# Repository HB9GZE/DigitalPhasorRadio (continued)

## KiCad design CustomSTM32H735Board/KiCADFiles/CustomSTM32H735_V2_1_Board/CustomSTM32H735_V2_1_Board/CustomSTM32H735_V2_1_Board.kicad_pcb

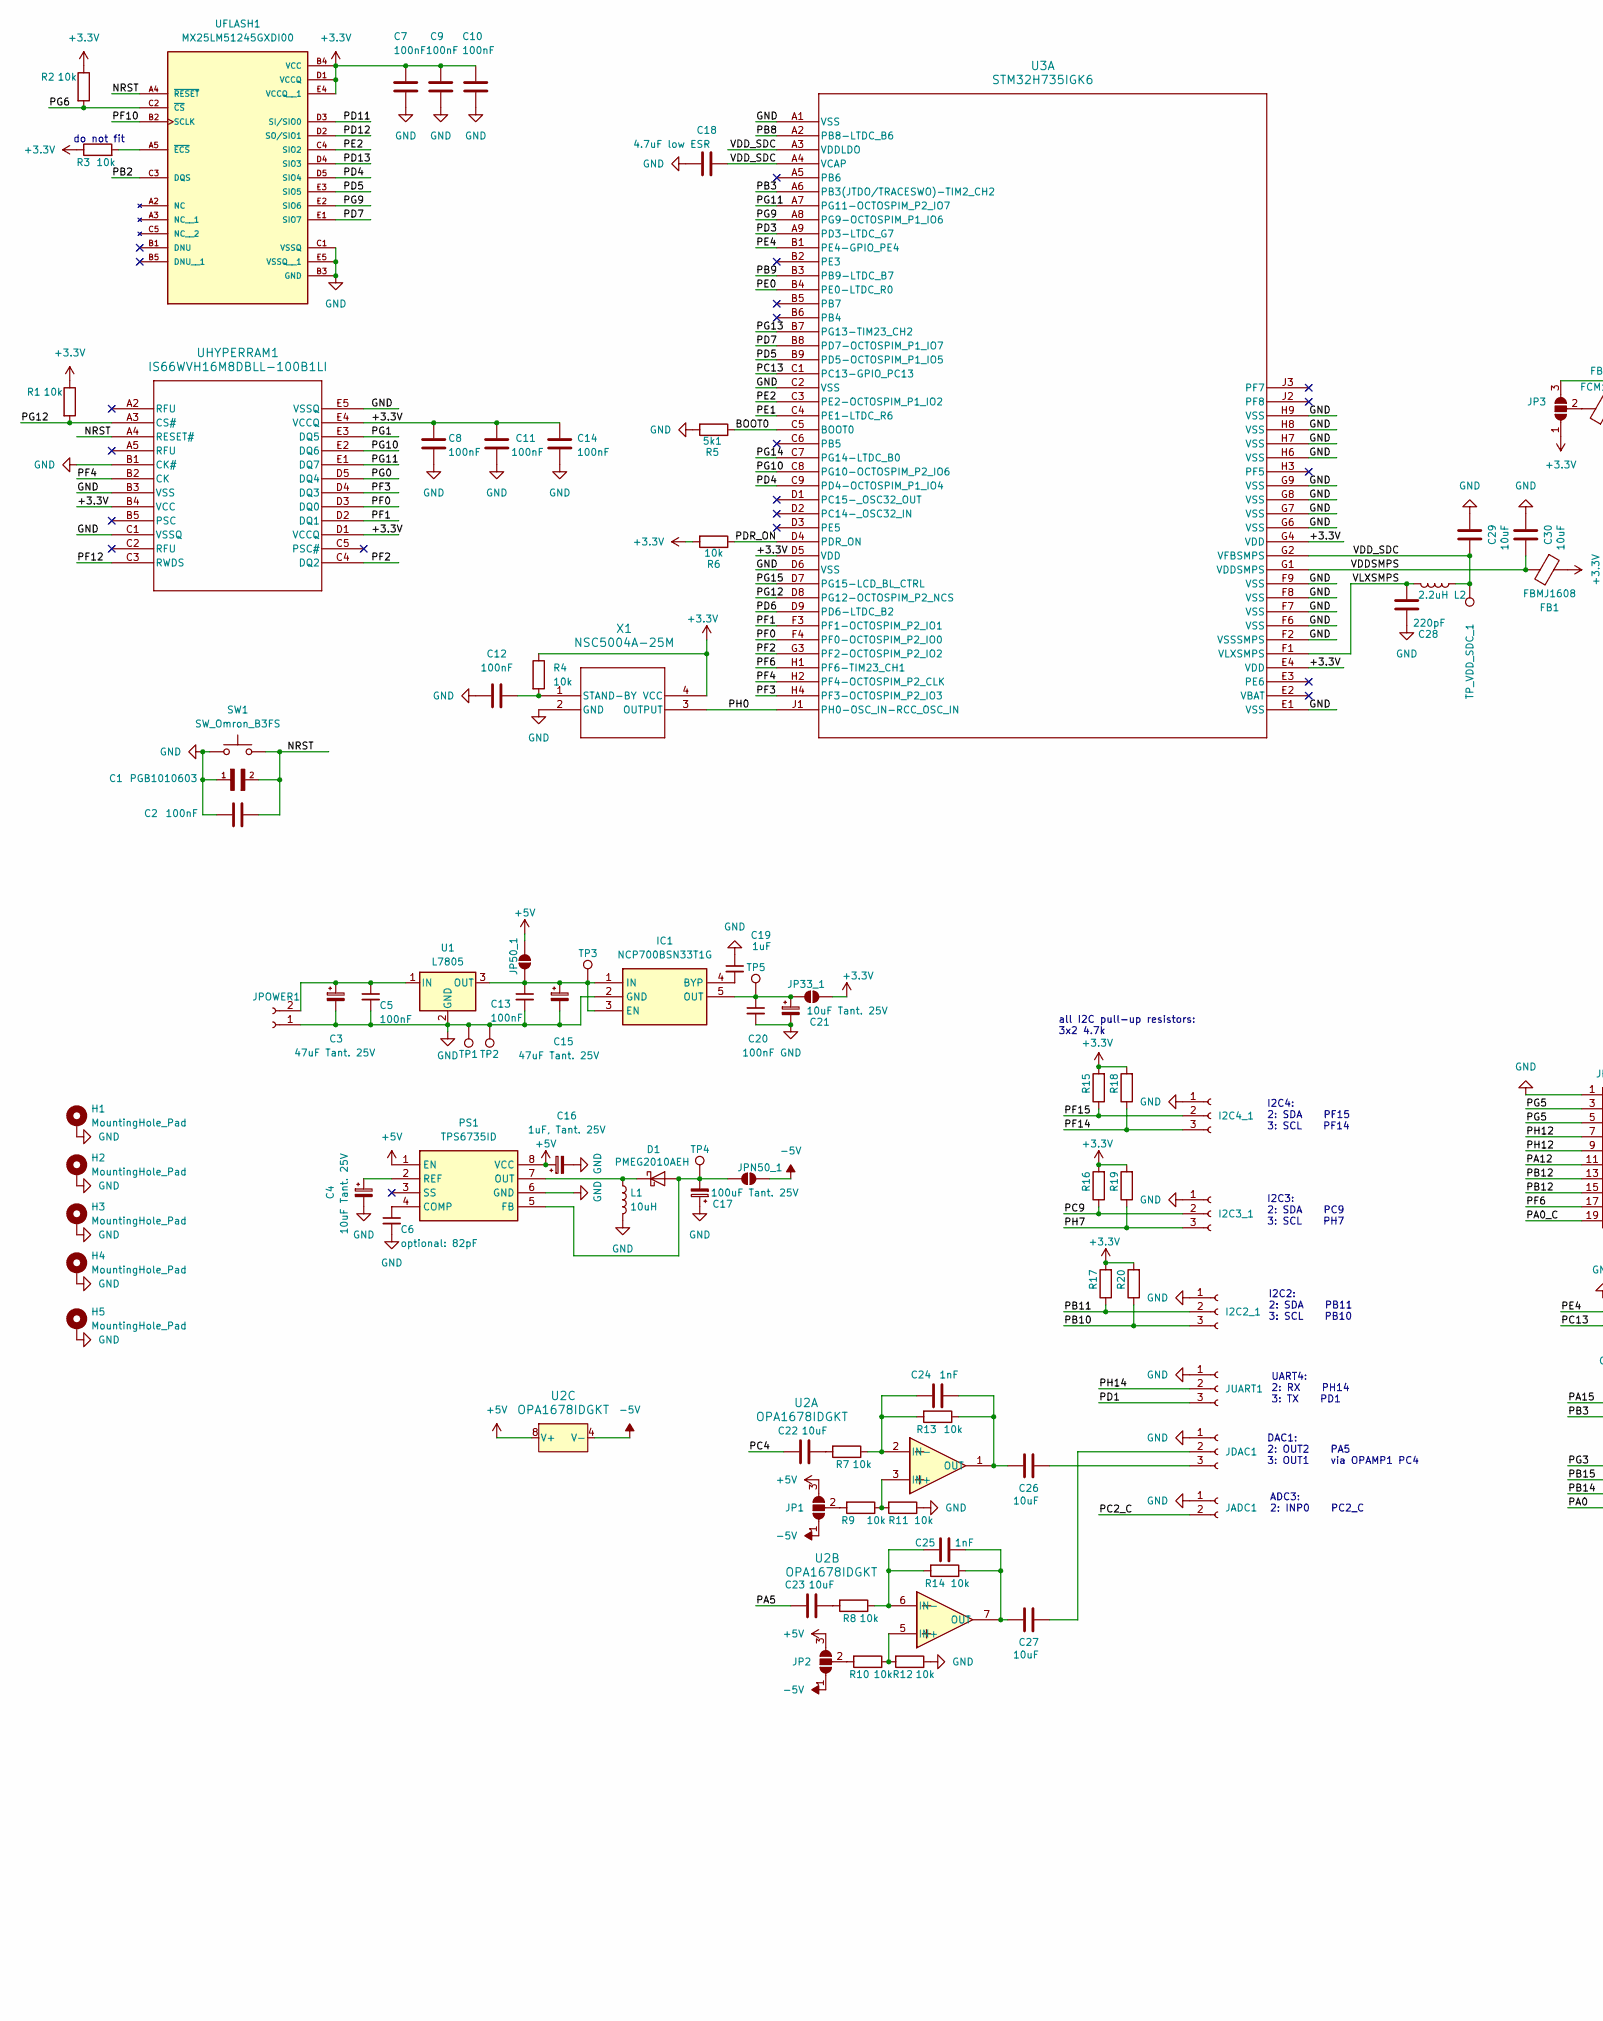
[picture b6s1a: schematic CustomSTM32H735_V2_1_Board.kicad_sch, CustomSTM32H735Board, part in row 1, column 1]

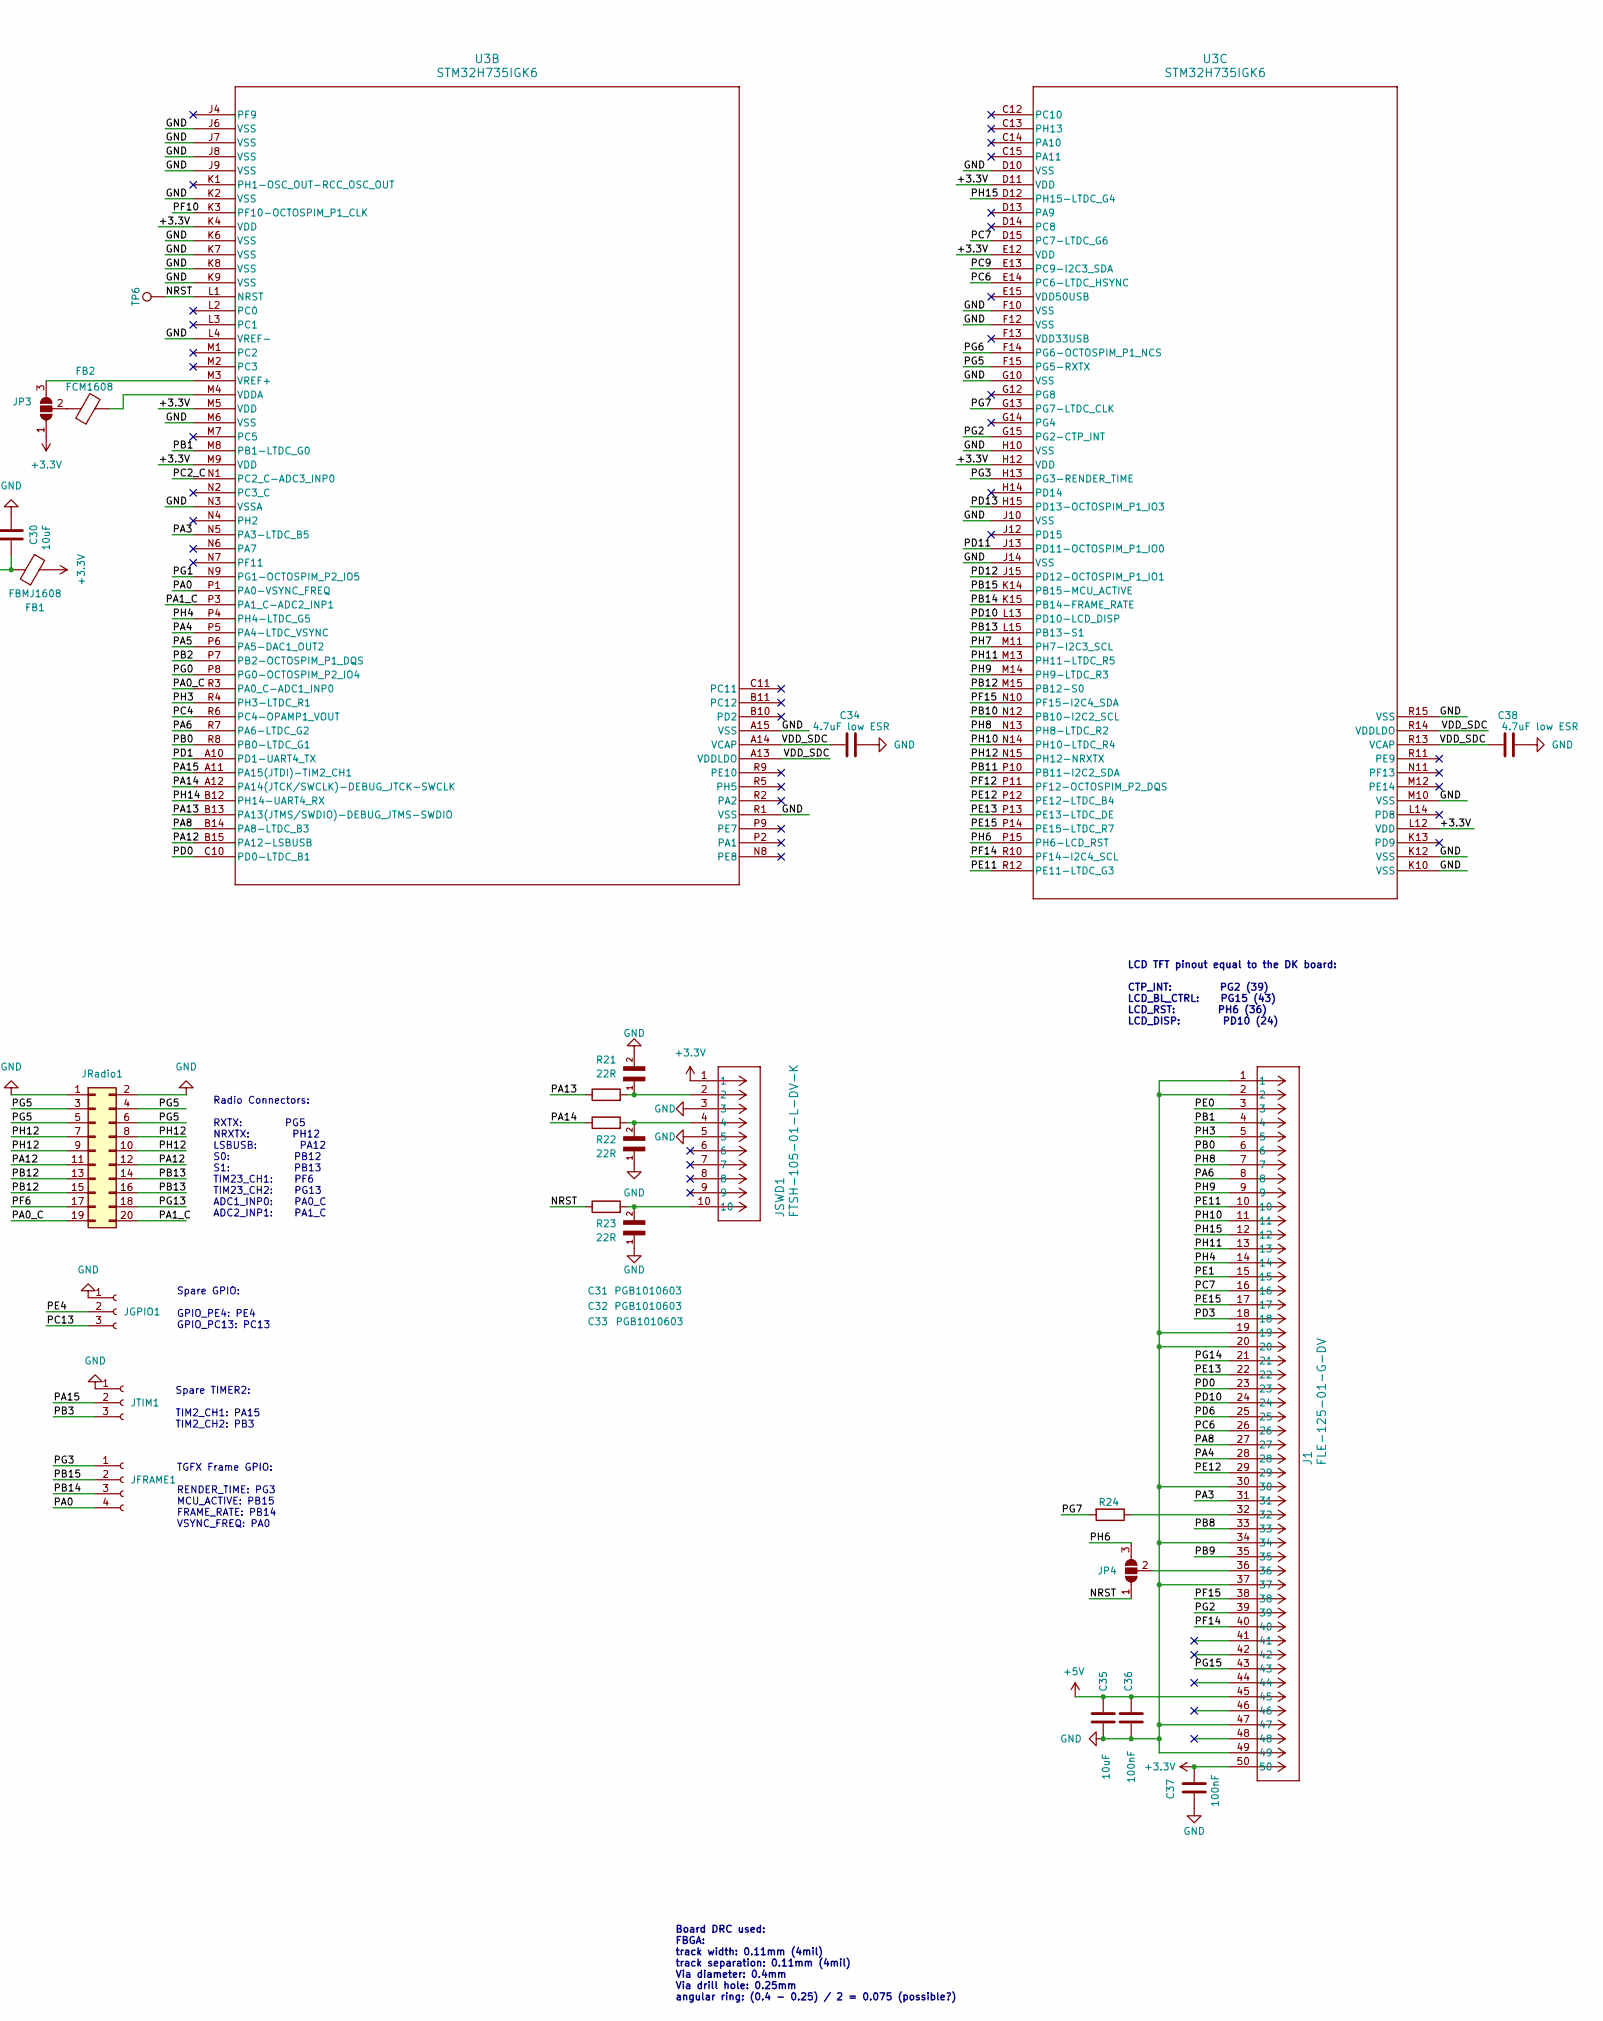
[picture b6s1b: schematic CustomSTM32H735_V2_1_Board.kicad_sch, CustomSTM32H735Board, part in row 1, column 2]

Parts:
C1, C31, C32, C33: PGB1010603; C_0603_1608Metric
C2, C5, C7, C8, C9, C10, C11, C12, C13, C14, C20, C36, C37: 100nF; C_0805_2012Metric_Pad1.18x1.45mm_HandSolder
C3, C15: 47uF Tant. 25V; CP_EIA-6032-20_AVX-F_Pad2.25x2.35mm_HandSolder
C4, C21: 10uF Tant. 25V; CP_EIA-6032-20_AVX-F_Pad2.25x2.35mm_HandSolder
C6: optional: 82pF; C_0805_2012Metric_Pad1.18x1.45mm_HandSolder
C16: 1uF, Tant. 25V; CP_EIA-6032-20_AVX-F_Pad2.25x2.35mm_HandSolder
C17: 100uF Tant. 25V; CP_EIA-6032-20_AVX-F_Pad2.25x2.35mm_HandSolder
C18, C34, C38: 4.7uF low ESR; C_0805_2012Metric_Pad1.18x1.45mm_HandSolder
C19: 1uF; C_0805_2012Metric_Pad1.18x1.45mm_HandSolder
C22, C23, C26, C27, C29, C30, C35: 10uF; C_0805_2012Metric_Pad1.18x1.45mm_HandSolder
C24, C25: 1nF; C_0805_2012Metric_Pad1.18x1.45mm_HandSolder
C28: 220pF; C_0805_2012Metric_Pad1.18x1.45mm_HandSolder
D1: PMEG2010AEH; D_SOD-123F
FB1: FBMJ1608; L_0603_1608Metric_Pad1.05x0.95mm_HandSolder
FB2: FCM1608; L_0603_1608Metric_Pad1.05x0.95mm_HandSolder
H1, H2, H3, H4, H5: MountingHole_Pad; MountingHole_3.2mm_M3_Pad_TopBottom
I2C2_1, I2C3_1, I2C4_1: Conn_01x03_Socket; JST_XH_B3B-XH-A_1x03_P2.50mm_Vertical
IC1: NCP700BSN33T1G; SOT95P275X120-5N; Manufacturer_Part_Number NCP700BSN33T1G; Mouser Part Number 863-NCP700BSN33T1G
J1: FLE-125-01-G-DV; CON50_2X25_UF_FLE_SAI
JADC1: Conn_01x02_Socket; JST_XH_B2B-XH-A_1x02_P2.50mm_Vertical
JDAC1: Conn_01x03_Socket; JST_XH_B3B-XH-A_1x03_P2.50mm_Vertical
JFRAME1: Conn_01x04_Socket; JST_XH_B4B-XH-A_1x04_P2.50mm_Vertical
JGPIO1: Conn_01x03_Socket; JST_XH_B3B-XH-A_1x03_P2.50mm_Vertical
JP1, JP2, JP3, JP4: SolderJumper_3_Open; SolderJumper-3_P1.3mm_Open_Pad1.0x1.5mm_NumberLabels
JP33_1, JP50_1: SolderJumper_2_Open; SolderJumper-2_P1.3mm_Open_Pad1.0x1.5mm
JPN50_1: SolderJumper_2_Open; SolderJumper-2_P1.3mm_Open_Pad1.0x1.5mm
JPOWER1: Conn_01x02_Socket; JST_XH_B2B-XH-A_1x02_P2.50mm_Vertical
JRadio1: Conn_02x10_Odd_Even; IDC-Header_2x10_P2.54mm_Vertical
JSWD1: FTSH-105-01-L-DV-K; CON10_2X5_DUK_FTSH_SAI-M
JTIM1: Conn_01x03_Socket; JST_XH_B3B-XH-A_1x03_P2.50mm_Vertical
JUART1: Conn_01x03_Socket; JST_XH_B3B-XH-A_1x03_P2.50mm_Vertical
L1: 10uH; L_1812_4532Metric_Pad1.30x3.40mm_HandSolder
L2: 2.2uH; L_Murata_DFE201610P
PS1: TPS6735ID; SOIC127P600X175-8N; Manufacturer_Part_Number TPS6735ID; Mouser Part Number 595-TPS6735ID
R1, R2, R3, R4, R6, R7, R8, R9, R10, R11, R12, R13, R14: 10k; R_0805_2012Metric_Pad1.20x1.40mm_HandSolder
R5: 5k1; R_0805_2012Metric_Pad1.20x1.40mm_HandSolder
R15, R16, R17, R18, R19, R20: 4.7k; R_0805_2012Metric_Pad1.20x1.40mm_HandSolder
R21, R22, R23: 22R; R_0805_2012Metric_Pad1.20x1.40mm_HandSolder
R24: 0R; R_0805_2012Metric_Pad1.20x1.40mm_HandSolder
SW1: SW_Omron_B3FS; SW_SPST_Omron_B3FS-100xP
TP1, TP2, TP3, TP4, TP5, TP6: TestPoint; Pin_D0.7mm_L6.5mm_W1.8mm_FlatFork
TP_VDD_SDC_1: TestPoint; Pin_D0.7mm_L6.5mm_W1.8mm_FlatFork
U1: L7805; TO-220-3_Horizontal_TabDown_GND_Pad
U2: OPA1678IDGKT; OPA1678_L
U3: STM32H735IGK6; BGA_735IGK6_STM
UFLASH1: MX25LM51245GXDI00; BGA24C100P5X5_600X800X120; PARTREV 1.1
UHYPERRAM1: IS66WVH16M8DBLL-100B1LI; TFBGA24_6X8_ISI
X1: NSC5004A-25M; NSC5004_NDK

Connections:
+3.3V: C7.1, C8.1, C9.1, C10.1, C11.1, C14.1, C37.1, FB1.1, J1.50, JP3.1 (A), JP33_1.2 (B), JSWD1.1, R1.1, R2.1, R3.1, R4.1, R6.2, R15.2, R16.2, R17.2, R18.2, R19.2, R20.2, U3.D5 (VDD), U3.D11 (VDD), U3.E4 (VDD), U3.E12 (VDD), U3.G4 (VDD), U3.H12 (VDD), U3.K4 (VDD), U3.L12 (VDD), U3.M5 (VDD), U3.M9 (VDD), UFLASH1.B4 (VCC), UFLASH1.D1 (VCCQ), UFLASH1.E4 (VCCQ__1), UHYPERRAM1.B4 (VCC), UHYPERRAM1.D1 (VCCQ), UHYPERRAM1.E4 (VCCQ), X1.4 (VCC)
+5V: C16.1, C35.1, C36.1, J1.45, JP1.3 (B), JP2.3 (B), JP50_1.2 (B), PS1.1 (EN), PS1.8 (VCC), U2.8 (V+)
-5V: JP1.1 (A), JP2.1 (A), JPN50_1.2 (B), U2.4 (V-)
/BOOT0: R5.1, U3.C5 (BOOT0)
/NRST: C1.2, C2.1, JP4.1 (A), R23.1, SW1.2, TP6.1, U3.L1 (NRST), UFLASH1.A4 (~RESET), UHYPERRAM1.A4 (RESET#)
/PA0: JFRAME1.4, U3.P1 (PA0-VSYNC_FREQ)
/PA0_C: JRadio1.19, U3.R3 (PA0_C-ADC1_INP0)
/PA1_C: JRadio1.20, U3.P3 (PA1_C-ADC2_INP1)
/PA3: J1.31, U3.N5 (PA3-LTDC_B5)
/PA4: J1.28, U3.P5 (PA4-LTDC_VSYNC)
/PA5: C23.1, U3.P6 (PA5-DAC1_OUT2)
/PA6: J1.8, U3.R7 (PA6-LTDC_G2)
/PA8: J1.27, U3.B14 (PA8-LTDC_B3)
/PA12: JRadio1.11, JRadio1.12, U3.B15 (PA12-LSBUSB)
/PA13: R21.1, U3.B13 (PA13(JTMS/SWDIO)-DEBUG_JTMS-SWDIO)
/PA14: R22.1, U3.A12 (PA14(JTCK/SWCLK)-DEBUG_JTCK-SWCLK)
/PA15: JTIM1.2, U3.A11 (PA15(JTDI)-TIM2_CH1)
/PB0: J1.6, U3.R8 (PB0-LTDC_G1)
/PB1: J1.4, U3.M8 (PB1-LTDC_G0)
/PB2: U3.P7 (PB2-OCTOSPIM_P1_DQS), UFLASH1.C3 (DQS)
/PB3: JTIM1.3, U3.A6 (PB3(JTDO/TRACESWO)-TIM2_CH2)
/PB8: J1.33, U3.A2 (PB8-LTDC_B6)
/PB9: J1.35, U3.B3 (PB9-LTDC_B7)
/PB10: I2C2_1.3, R20.1, U3.N12 (PB10-I2C2_SCL)
/PB11: I2C2_1.2, R17.1, U3.P10 (PB11-I2C2_SDA)
/PB12: JRadio1.13, JRadio1.15, U3.M15 (PB12-S0)
/PB13: JRadio1.14, JRadio1.16, U3.L15 (PB13-S1)
/PB14: JFRAME1.3, U3.K15 (PB14-FRAME_RATE)
/PB15: JFRAME1.2, U3.K14 (PB15-MCU_ACTIVE)
/PC2_C: JADC1.2, U3.N1 (PC2_C-ADC3_INP0)
/PC4: C22.1, U3.R6 (PC4-OPAMP1_VOUT)
/PC6: J1.26, U3.E14 (PC6-LTDC_HSYNC)
/PC7: J1.16, U3.D15 (PC7-LTDC_G6)
/PC9: I2C3_1.2, R16.1, U3.E13 (PC9-I2C3_SDA)
/PC13: JGPIO1.3, U3.C1 (PC13-GPIO_PC13)
/PD0: J1.23, U3.C10 (PD0-LTDC_B1)
/PD1: JUART1.3, U3.A10 (PD1-UART4_TX)
/PD3: J1.18, U3.A9 (PD3-LTDC_G7)
/PD4: U3.C9 (PD4-OCTOSPIM_P1_IO4), UFLASH1.D5 (SIO4)
/PD5: U3.B9 (PD5-OCTOSPIM_P1_IO5), UFLASH1.E3 (SIO5)
/PD6: J1.25, U3.D9 (PD6-LTDC_B2)
/PD7: U3.B8 (PD7-OCTOSPIM_P1_IO7), UFLASH1.E1 (SIO7)
/PD10: J1.24, U3.L13 (PD10-LCD_DISP)
/PD11: U3.J13 (PD11-OCTOSPIM_P1_IO0), UFLASH1.D3 (SI/SIO0)
/PD12: U3.J15 (PD12-OCTOSPIM_P1_IO1), UFLASH1.D2 (SO/SIO1)
/PD13: U3.H15 (PD13-OCTOSPIM_P1_IO3), UFLASH1.D4 (SIO3)
/PDR_ON: R6.1, U3.D4 (PDR_ON)
/PE0: J1.3, U3.B4 (PE0-LTDC_R0)
/PE1: J1.15, U3.C4 (PE1-LTDC_R6)
/PE2: U3.C3 (PE2-OCTOSPIM_P1_IO2), UFLASH1.C4 (SIO2)
/PE4: JGPIO1.2, U3.B1 (PE4-GPIO_PE4)
/PE11: J1.10, U3.R12 (PE11-LTDC_G3)
/PE12: J1.29, U3.P12 (PE12-LTDC_B4)
/PE13: J1.22, U3.P13 (PE13-LTDC_DE)
/PE15: J1.17, U3.P14 (PE15-LTDC_R7)
/PF0: U3.F4 (PF0-OCTOSPIM_P2_IO0), UHYPERRAM1.D3 (DQ0)
/PF1: U3.F3 (PF1-OCTOSPIM_P2_IO1), UHYPERRAM1.D2 (DQ1)
/PF2: U3.G3 (PF2-OCTOSPIM_P2_IO2), UHYPERRAM1.C4 (DQ2)
/PF3: U3.H4 (PF3-OCTOSPIM_P2_IO3), UHYPERRAM1.D4 (DQ3)
/PF4: U3.H2 (PF4-OCTOSPIM_P2_CLK), UHYPERRAM1.B2 (CK)
/PF6: JRadio1.17, U3.H1 (PF6-TIM23_CH1)
/PF10: U3.K3 (PF10-OCTOSPIM_P1_CLK), UFLASH1.B2 (SCLK)
/PF12: U3.P11 (PF12-OCTOSPIM_P2_DQS), UHYPERRAM1.C3 (RWDS)
/PF14: I2C4_1.3, J1.40, R18.1, U3.R10 (PF14-I2C4_SCL)
/PF15: I2C4_1.2, J1.38, R15.1, U3.N10 (PF15-I2C4_SDA)
/PG0: U3.P8 (PG0-OCTOSPIM_P2_IO4), UHYPERRAM1.D5 (DQ4)
/PG1: U3.N9 (PG1-OCTOSPIM_P2_IO5), UHYPERRAM1.E3 (DQ5)
/PG2: J1.39, U3.G15 (PG2-CTP_INT)
/PG3: JFRAME1.1, U3.H13 (PG3-RENDER_TIME)
/PG5: JRadio1.3, JRadio1.4, JRadio1.5, JRadio1.6, U3.F15 (PG5-RXTX)
/PG6: R2.2, U3.F14 (PG6-OCTOSPIM_P1_NCS), UFLASH1.C2 (~CS)
/PG7: R24.2, U3.G13 (PG7-LTDC_CLK)
/PG9: U3.A8 (PG9-OCTOSPIM_P1_IO6), UFLASH1.E2 (SIO6)
/PG10: U3.C8 (PG10-OCTOSPIM_P2_IO6), UHYPERRAM1.E2 (DQ6)
/PG11: U3.A7 (PG11-OCTOSPIM_P2_IO7), UHYPERRAM1.E1 (DQ7)
/PG12: R1.2, U3.D8 (PG12-OCTOSPIM_P2_NCS), UHYPERRAM1.A3 (CS#)
/PG13: JRadio1.18, U3.B7 (PG13-TIM23_CH2)
/PG14: J1.21, U3.C7 (PG14-LTDC_B0)
/PG15: J1.43, U3.D7 (PG15-LCD_BL_CTRL)
/PH0: U3.J1 (PH0-OSC_IN-RCC_OSC_IN), X1.3 (OUTPUT)
/PH3: J1.5, U3.R4 (PH3-LTDC_R1)
/PH4: J1.14, U3.P4 (PH4-LTDC_G5)
/PH6: JP4.3 (B), U3.P15 (PH6-LCD_RST)
/PH7: I2C3_1.3, R19.1, U3.M11 (PH7-I2C3_SCL)
/PH8: J1.7, U3.N13 (PH8-LTDC_R2)
/PH9: J1.9, U3.M14 (PH9-LTDC_R3)
/PH10: J1.11, U3.N14 (PH10-LTDC_R4)
/PH11: J1.13, U3.M13 (PH11-LTDC_R5)
/PH12: JRadio1.7, JRadio1.8, JRadio1.9, JRadio1.10, U3.N15 (PH12-NRXTX)
/PH14: JUART1.2, U3.B12 (PH14-UART4_RX)
/PH15: J1.12, U3.D12 (PH15-LTDC_G4)
/VDDSMPS: C30.1, FB1.2, U3.G1 (VDDSMPS)
/VDD_SDC: C18.2, C29.1, C34.2, C38.2, L2.1, TP_VDD_SDC_1.1, U3.A3 (VDDLDO), U3.A4 (VCAP), U3.A13 (VDDLDO), U3.A14 (VCAP), U3.G2 (VFBSMPS), U3.R13 (VCAP), U3.R14 (VDDLDO)
/VLXSMPS: C28.2, L2.2, U3.F1 (VLXSMPS)
GND: C1.1, C2.2, C3.2, C4.2, C5.2, C6.2, C7.2, C8.2, C9.2, C10.2, C11.2, C12.1, C13.2, C14.2, C15.2, C16.2, C17.1, C18.1, C19.1, C20.2, C21.2, C28.1, C29.2, C30.2, C31.2, C32.1, C33.1, C34.1, C35.2, C36.2, C37.2, C38.1, H1.1, H2.1, H3.1, H4.1, H5.1, I2C2_1.1, I2C3_1.1, I2C4_1.1, IC1.2 (GND), J1.1, J1.2, J1.19, J1.20, J1.30, J1.34, J1.37, J1.47, J1.49, JADC1.1, JDAC1.1, JGPIO1.1, JPOWER1.1, JRadio1.1, JRadio1.2, JSWD1.3, JSWD1.5, JTIM1.1, JUART1.1, L1.2, PS1.6 (GND), R5.2, R11.1, R12.1, SW1.1, TP1.1, TP2.1, U1.2 (GND), U1.4, U3.A1 (VSS), U3.A15 (VSS), U3.C2 (VSS), U3.D6 (VSS), U3.D10 (VSS), U3.E1 (VSS), U3.F2 (VSSSMPS), U3.F6 (VSS), U3.F7 (VSS), U3.F8 (VSS), U3.F9 (VSS), U3.F10 (VSS), U3.F12 (VSS), U3.G6 (VSS), U3.G7 (VSS), U3.G8 (VSS), U3.G9 (VSS), U3.G10 (VSS), U3.H6 (VSS), U3.H7 (VSS), U3.H8 (VSS), U3.H9 (VSS), U3.H10 (VSS), U3.J6 (VSS), U3.J7 (VSS), U3.J8 (VSS), U3.J9 (VSS), U3.J10 (VSS), U3.J14 (VSS), U3.K2 (VSS), U3.K6 (VSS), U3.K7 (VSS), U3.K8 (VSS), U3.K9 (VSS), U3.K10 (VSS), U3.K12 (VSS), U3.L4 (VREF-), U3.M6 (VSS), U3.M10 (VSS), U3.N3 (VSSA), U3.R1 (VSS), U3.R15 (VSS), UFLASH1.B3 (GND), UFLASH1.C1 (VSSQ), UFLASH1.E5 (VSSQ__1), UHYPERRAM1.B1 (CK#), UHYPERRAM1.B3 (VSS), UHYPERRAM1.C1 (VSSQ), UHYPERRAM1.E5 (VSSQ), X1.2 (GND)
unnamed: C22.2, R7.2
unnamed: C23.2, R8.2
unnamed: C31.1, JSWD1.2, R21.2
unnamed: C32.2, JSWD1.4, R22.2
unnamed: C33.2, JSWD1.10, R23.2
unnamed: C17.2, D1.2 (A), JPN50_1.1 (A), PS1.5 (FB), TP4.1
unnamed: D1.1 (K), L1.1, PS1.7 (OUT)
unnamed: C19.2, IC1.4 (BYP)
unnamed: C13.1, C15.1, IC1.1 (IN), IC1.3 (EN), JP50_1.1 (A), TP3.1, U1.3 (OUT)
unnamed: C20.1, C21.1, IC1.5 (OUT), JP33_1.1 (A), TP5.1
unnamed: J1.32, R24.1
unnamed: C27.2, JDAC1.2
unnamed: C26.2, JDAC1.3
unnamed: JP1.2 (C), R9.2
unnamed: JP2.2 (C), R10.2
unnamed: JP3.3 (B), U3.M3 (VREF+)
unnamed: FB2.1, JP3.2 (C)
unnamed: J1.36, JP4.2 (C)
unnamed: C3.1, C5.1, JPOWER1.2, U1.1 (IN)
unnamed: C6.1, PS1.4 (COMP)
unnamed: C4.1, PS1.2 (REF)
unnamed: R9.1, R11.2, U2.3 (IN+)
unnamed: C24.1, R7.1, R13.2, U2.2 (IN-)
unnamed: C24.2, C26.1, R13.1, U2.1 (OUT)
unnamed: R10.1, R12.2, U2.5 (IN+)
unnamed: C25.1, R8.1, R14.2, U2.6 (IN-)
unnamed: C25.2, C27.1, R14.1, U2.7 (OUT)
unnamed: FB2.2, U3.M4 (VDDA)
unnamed: R3.2, UFLASH1.A5 (~ECS)
unnamed: C12.2, R4.2, X1.1 (STAND-BY)

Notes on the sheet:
TGFX Frame GPIO: RENDER_TIME: PG3 MCU_ACTIVE: PB15 FRAME_RATE: PB14 VSYNC_FREQ: PA0
Spare TIMER2: TIM2_CH1: PA15 TIM2_CH2: PB3
DAC1: 2: OUT2 PA5 3: OUT1 via OPAMP1 PC4
Radio Connectors: RXTX: PG5 NRXTX: PH12 LSBUSB: PA12 S0: PB12 S1: PB13 TIM23_CH1: PF6 TIM23_CH2: PG13 ADC1_INP0: PA0_C ADC2_INP1: PA1_C
LCD TFT pinout equal to the DK board: CTP_INT: PG2 (39) LCD_BL_CTRL: PG15 (43) LCD_RST: PH6 (36) LCD_DISP: PD10 (24)
I2C2: 2: SDA PB11 3: SCL PB10
Spare GPIO: GPIO_PE4: PE4 GPIO_PC13: PC13
do not fit
UART4: 2: RX PH14 3: TX PD1
ADC3: 2: INP0 PC2_C
Board DRC used: FBGA: track width: 0.11mm (4mil) track separation: 0.11mm (4mil) Via diameter: 0.4mm Via drill hole: 0.25mm angular ring: (0.4 - 0.25) / 2 = 0.075 (possible?)
I2C3: 2: SDA PC9 3: SCL PH7
all I2C pull-up resistors: 3x2 4.7k
I2C4: 2: SDA PF15 3: SCL PF14

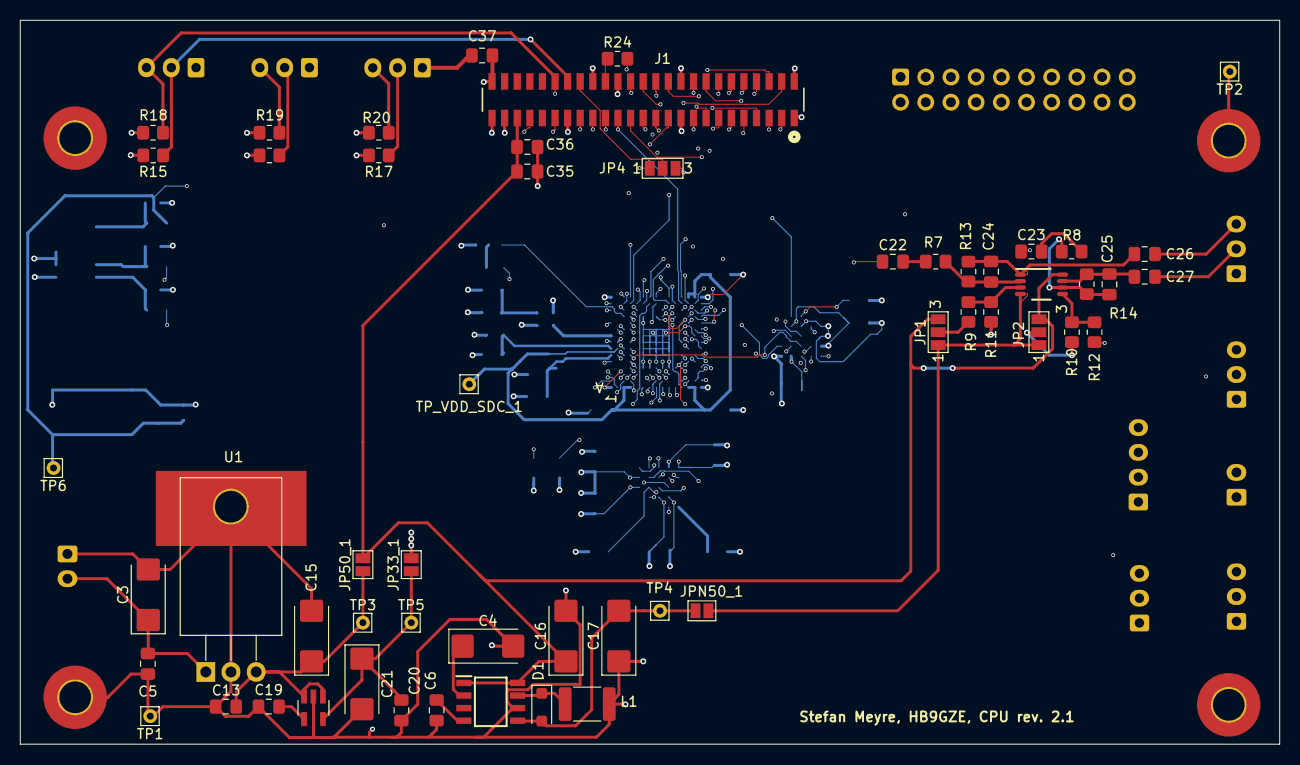
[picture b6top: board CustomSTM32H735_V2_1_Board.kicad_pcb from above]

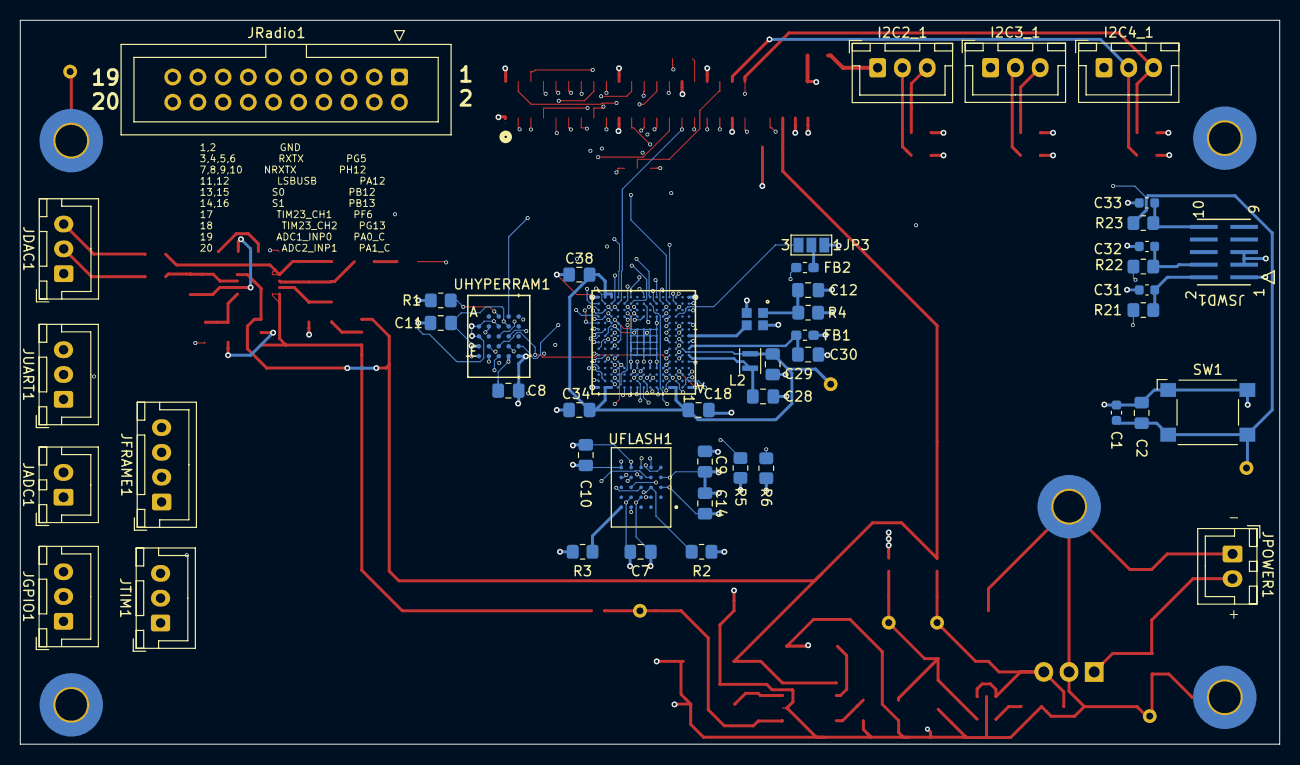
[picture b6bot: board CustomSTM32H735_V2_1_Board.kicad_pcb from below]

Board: 6 copper layers, 127.0 x 73.0 mm, 108 parts (48 on the bottom side), 125 nets.

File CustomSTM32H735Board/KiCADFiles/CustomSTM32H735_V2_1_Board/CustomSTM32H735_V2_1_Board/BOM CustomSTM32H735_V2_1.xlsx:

Id | Designator | Footprint | Quantity | Designation | Supplier and ref | Column1 | _1
1 | D1 | D_SOD-123F | 1 | PMEG2010AEH
2 | R14,R8,R11,R13,R12,R10,R9,R7,R4,R2,R3,R1,R6 | R_0805_2012Metric_Pad1.20x1.40mm_HandSolder | 13 | 10k
3 | TP1,TP2,TP_VDD_SDC_1,TP4,TP3 | Pin_D0.7mm_L6.5mm_W1.8mm_FlatFork | 5 | TestPoint
4 | U2 | OPA1678_L | 1 | OPA1678IDGKT
5 | R19,R17,R16,R18,R20,R15 | R_0805_2012Metric_Pad1.20x1.40mm_HandSolder | 6 | 4.7k
6 | C3,C15 | CP_EIA-6032-20_AVX-F_Pad2.25x2.35mm_HandSolder | 2 | 47uF Tant. 25V
7 | IC1 | SOT95P275X120-5N | 1 | NCP700BSN33T1G
8 | C21,C4 | CP_EIA-6032-20_AVX-F_Pad2.25x2.35mm_HandSolder | 2 | 10uF Tant. 25V
9 | C25,C24 | C_0805_2012Metric_Pad1.18x1.45mm_HandSolder | 2 | 1nF
10 | U1 | TO-220-3_Horizontal_TabDown_GND_Pad | 1 | L7805
11 | L1 | L_1812_4532Metric_Pad1.30x3.40mm_HandSolder | 1 | 10uH
12 | C35,C23,C22,C26,C27,C30,C29 | C_0805_2012Metric_Pad1.18x1.45mm_HandSolder | 7 | 10uF
13 | C5,C20,C13,C37,C36,C2,C10,C12,C11,C8,C14,C7,C9 | C_0805_2012Metric_Pad1.18x1.45mm_HandSolder | 13 | 100nF
14 | C17 | CP_EIA-6032-20_AVX-F_Pad2.25x2.35mm_HandSolder | 1 | 100uF Tant. 25V
15 | J1 | CON50_2X25_UF_FLE_SAI | 1 | FLE-125-01-G-DV
16 | PS1 | SOIC127P600X175-8N | 1 | TPS6735ID
17 | C19 | C_0805_2012Metric_Pad1.18x1.45mm_HandSolder | 1 | 1uF
18 | C6 | C_0805_2012Metric_Pad1.18x1.45mm_HandSolder | 1 | optional: 82pF
19 | R24 | R_0805_2012Metric_Pad1.20x1.40mm_HandSolder | 1 | 0R
20 | C16 | CP_EIA-6032-20_AVX-F_Pad2.25x2.35mm_HandSolder | 1 | 1uF, Tant. 25V
21 | R23,R21,R22 | R_0805_2012Metric_Pad1.20x1.40mm_HandSolder | 3 | 22R
22 | C1,C31,C32,C33 | C_0603_1608Metric | 4 | PGB1010603
23 | I2C2_1,JGPIO1,JDAC1,I2C4_1,JUART1,JTIM1,I2C3_1 | JST_XH_B3B-XH-A_1x03_P2.50mm_Vertical | 7 | Conn_01x03_Socket
24 | JSWD1 | CON10_2X5_DUK_FTSH_SAI-M | 1 | FTSH-105-01-L-DV-K
25 | L2 | L_Murata_DFE201610P | 1 | 2.2uH
26 | JRadio1 | IDC-Header_2x10_P2.54mm_Vertical | 1 | Conn_02x10_Odd_Even
27 | FB1 | L_0603_1608Metric_Pad1.05x0.95mm_HandSolder | 1 | FBMJ1608
28 | JADC1,JPOWER1 | JST_XH_B2B-XH-A_1x02_P2.50mm_Vertical | 2 | Conn_01x02_Socket
29 | R5 | R_0805_2012Metric_Pad1.20x1.40mm_HandSolder | 1 | 5k1
30 | FB2 | L_0603_1608Metric_Pad1.05x0.95mm_HandSolder | 1 | FCM1608
31 | C34,C18,C38 | C_0805_2012Metric_Pad1.18x1.45mm_HandSolder | 3 | 4.7uF low ESR
32 | JFRAME1 | JST_XH_B4B-XH-A_1x04_P2.50mm_Vertical | 1 | Conn_01x04_Socket
33 | SW1 | SW_SPST_Omron_B3FS-100xP | 1 | SW_Omron_B3FS
34 | UHYPERRAM1 | TFBGA24_6X8_ISI | 1 | IS66WVH16M8DBLL-100B1LI
35 | UFLASH1 | BGA24C100P5X5_600X800X120 | 1 | MX25LM51245GXDI00
36 | C28 | C_0805_2012Metric_Pad1.18x1.45mm_HandSolder | 1 | 220pF
37 | X1 | NSC5004_NDK | 1 | NSC5004A-25M
38 | U3 | BGA_735IGK6_STM | 1 | STM32H735IGK6

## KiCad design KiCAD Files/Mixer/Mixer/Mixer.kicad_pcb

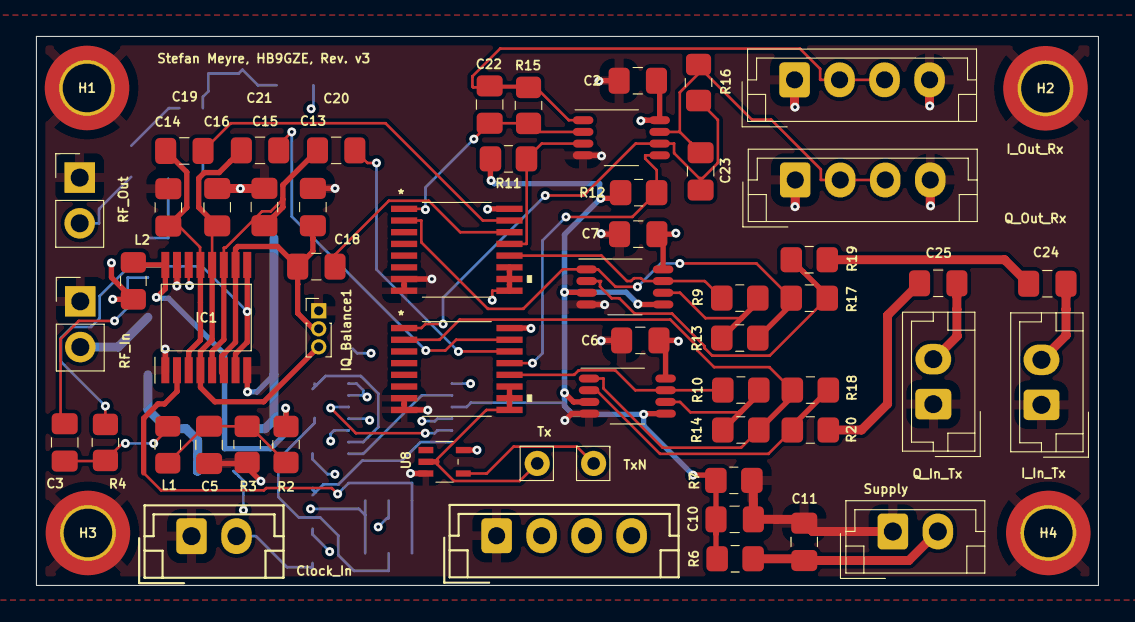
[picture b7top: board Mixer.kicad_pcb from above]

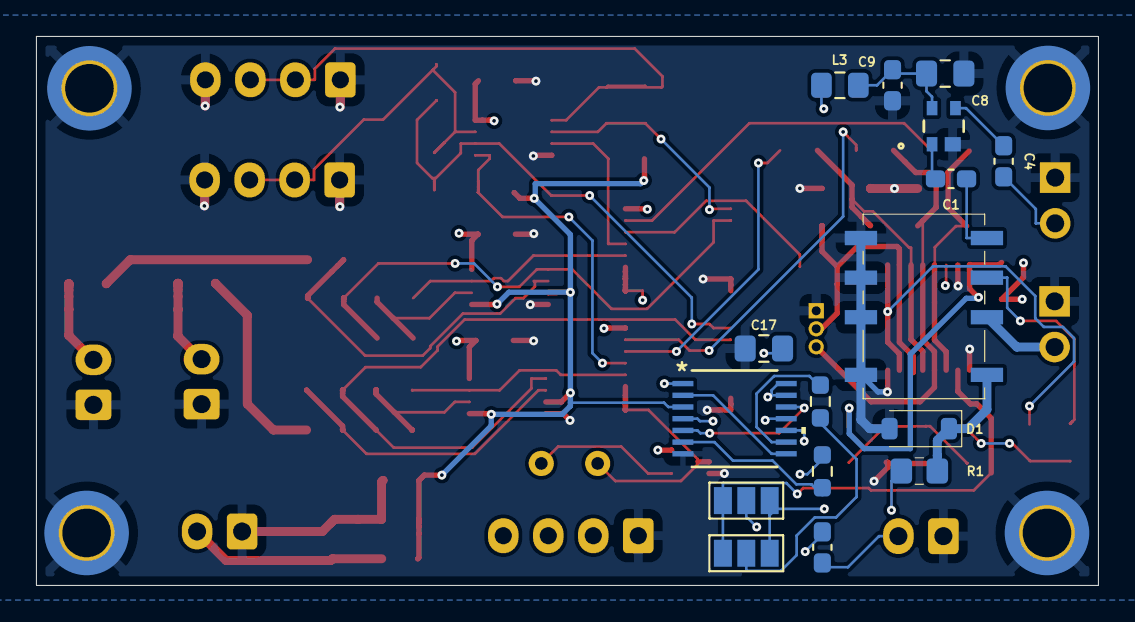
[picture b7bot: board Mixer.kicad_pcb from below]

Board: 4 copper layers, 59.0 x 30.5 mm, 77 parts (16 on the bottom side), 52 nets.

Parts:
C1, C4, C9, C12: 100nF; C_0603_1608Metric_Pad1.08x0.95mm_HandSolder
C2, C3, C5, C6, C7, C10, C11: 100nF; C_0805_2012Metric_Pad1.18x1.45mm_HandSolder
C8, C18, C19, C20, C21, C24, C25: 1uF; C_0805_2012Metric_Pad1.18x1.45mm_HandSolder
C13, C14, C15, C16: 47nF; C_0805_2012Metric_Pad1.18x1.45mm_HandSolder
C17: 10uF; C_0805_2012Metric_Pad1.18x1.45mm_HandSolder
C22, C23: 1.5nF; C_0805_2012Metric_Pad1.18x1.45mm_HandSolder
Clock_In: Conn_01x02_Socket; JST_EH_B2B-EH-A_1x02_P2.50mm_Vertical
D1: 1N4148W; D_SOD-123
H1, H2, H3, H4: MountingHole_Pad; MountingHole_2.7mm_M2.5_DIN965_Pad_TopBottom
IC1: FST3253MTCX; SOP65P640X110-16N
IQ_Balance1: Conn_01x03; PinHeader_1x03_P1.00mm_Vertical
I_In_Tx: Conn_01x02; JST_EH_B2B-EH-A_1x02_P2.50mm_Vertical
I_Out_Rx: Conn_01x04_Socket; JST_EH_B4B-EH-A_1x04_P2.50mm_Vertical
J1: Conn_01x04_Socket; JST_EH_B4B-EH-A_1x04_P2.50mm_Vertical
JP1, JP2: SolderJumper_3_Open; SolderJumper-3_P1.3mm_Open_Pad1.0x1.5mm_NumberLabels
K1: G6K-2F-Y DC3; G6K-2F-Y DC3_OMR
L1, L2, L3: 100u; L_0805_2012Metric_Pad1.15x1.40mm_HandSolder
Q_In_Tx: Conn_01x02; JST_EH_B2B-EH-A_1x02_P2.50mm_Vertical
Q_Out_Rx: Conn_01x04_Socket; JST_EH_B4B-EH-A_1x04_P2.50mm_Vertical
R1: 0R; R_0805_2012Metric_Pad1.20x1.40mm_HandSolder
R2, R3: 10k; R_0805_2012Metric_Pad1.20x1.40mm_HandSolder
R4: 47R; R_0805_2012Metric_Pad1.20x1.40mm_HandSolder
R5, R8: 100R; R_0603_1608Metric_Pad0.98x0.95mm_HandSolder
R6, R7: 1k; R_0805_2012Metric_Pad1.20x1.40mm_HandSolder
R9, R10, R11, R12, R13, R14, R15, R16, R17, R18, R19, R20: 10k 1%; R_0805_2012Metric_Pad1.20x1.40mm_HandSolder
RF_In: Conn_01x02; PinHeader_1x02_P2.54mm_Vertical
RF_Out: Conn_01x02; PinHeader_1x02_P2.54mm_Vertical
Supply: Conn_01x02_Socket; JST_EH_B2B-EH-A_1x02_P2.50mm_Vertical
Tx: TestPoint; Pin_D0.7mm_L6.5mm_W1.8mm_FlatFork
TxN: TestPoint; Pin_D0.7mm_L6.5mm_W1.8mm_FlatFork
U1: BGA420H6327XTSA1; PG-SOT343-4-1_INF
U2, U3, U4: OPA1678IDGKT; OPA1678_L
U5: SN74AC74PWR; 74AC74-L
U6, U7: 4053; TSSOP16_5P1X4P5_NEX
U8: NC7SZ04P5X; SC-88A-5_1P35X2P2_ONS

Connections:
+5V: C2.2, C6.2, C7.2, C11.2, C17.2, L2.1, L3.1, R6.2, Supply.2, U2.8 (V+), U3.8 (V+), U4.8 (V+), U5.1 (*1CLR), U5.4 (*1PRE), U5.10 (*2PRE), U5.13 (*2CLR), U5.14 (VCC), U6.16 (VDD), U7.16 (VDD), U8.5 (VCC)
/1: C13.2, C18.2, IC1.6 (1B1), IC1.10 (2B1), IQ_Balance1.2
/2: C15.2, C20.2, IC1.5 (1B2), IC1.11 (2B2)
/3: C16.2, C21.2, IC1.4 (1B3), IC1.12 (2B3), IQ_Balance1.3
/4: C14.2, C19.2, IC1.3 (1B4), IC1.13 (2B4)
/+2.5V: C10.2, C12.2, R6.1, R7.1, R11.2, R12.2, U3.3 (IN+), U3.5 (IN+), U4.3 (IN+), U4.5 (IN+), U5.3 (1CLK), U5.11 (2CLK)
/Clk_S0: JP2.2 (C), R8.1
/Clk_S1: JP1.2 (C), R5.2
/RF_IN_OUT: C3.1, K1.3
/RF_In: K1.2, RF_In.2
/RF_Out: C4.2, RF_Out.2
/S0: IC1.14 (S0), JP1.1 (A), JP2.1 (A)
/S1: IC1.2 (S1), JP1.3 (B), JP2.3 (B)
/Tx: J1.2, J1.3, Tx.1, U6.9 (C), U6.10 (B), U6.11 (A), U7.9 (C), U7.10 (B), U7.11 (A), U8.2 (A)
/TxN: J1.4, R1.2, TxN.1, U8.4 (Y)
GND: C2.1, C5.1, C6.1, C7.1, C8.1, C9.1, C10.1, C11.1, C13.1, C14.1, C15.1, C16.1, C17.1, Clock_In.1, D1.2 (A), H1.1, H2.1, H3.1, H4.1, IC1.1 (~OE1), IC1.8 (GND), IC1.15 (~OE2), IQ_Balance1.1, I_In_Tx.1, I_Out_Rx.1, I_Out_Rx.4, J1.1, K1.5, K1.6, K1.7, K1.8, Q_In_Tx.1, Q_Out_Rx.1, Q_Out_Rx.4, R3.2, R7.2, RF_In.1, RF_Out.1, Supply.1, U1.2 (GND), U2.4 (V-), U3.4 (V-), U4.4 (V-), U5.7 (GND), U6.7 (VEE), U6.8 (VSS), U7.7 (VEE), U7.8 (VSS), U8.3 (GND)
unnamed: C1.1, K1.4
unnamed: C3.2, L1.2, R4.1
unnamed: C5.2, L1.1, R2.2, R3.1
unnamed: C24.2, R19.2
unnamed: C25.2, R20.2
unnamed: C12.1, Clock_In.2
unnamed: D1.1 (K), K1.1, R1.1
unnamed: IC1.7 (1A), IC1.9 (2A), R4.2
unnamed: IC1.16 (VCC), L2.2, R2.1
unnamed: C24.1, I_In_Tx.2
unnamed: C22.1, I_Out_Rx.2, I_Out_Rx.3, R15.2, U2.1 (OUT)
unnamed: C25.1, Q_In_Tx.2
unnamed: C23.1, Q_Out_Rx.2, Q_Out_Rx.3, R16.2, U2.7 (OUT)
unnamed: C1.2, U1.1 (IN)
unnamed: C4.1, U1.3 (OUT)
unnamed: C8.2, C9.2, L3.2, U1.4 (VD)
unnamed: R11.1, U2.3 (IN+), U6.13 (X1)
unnamed: C22.2, R15.1, U2.2 (IN-), U6.1 (Y1)
unnamed: R12.1, U2.5 (IN+), U7.13 (X1)
unnamed: C23.2, R16.1, U2.6 (IN-), U7.1 (Y1)
unnamed: R17.2, R19.1, U3.2 (IN-)
unnamed: R13.2, R17.1, U3.1 (OUT), U6.2 (Y0)
unnamed: R9.2, R13.1, U3.6 (IN-)
unnamed: R9.1, U3.7 (OUT), U6.12 (X0)
unnamed: R18.2, R20.1, U4.2 (IN-)
unnamed: R14.2, R18.1, U4.1 (OUT), U7.2 (Y0)
unnamed: R10.2, R14.1, U4.6 (IN-)
unnamed: R10.1, U4.7 (OUT), U7.12 (X0)
unnamed: U5.5 (1Q), U5.12 (2D)
unnamed: R8.2, U5.9 (2Q)
unnamed: R5.1, U5.6 (*1Q)
unnamed: U5.2 (1D), U5.8 (*2Q)
unnamed: C18.1, U6.14 (X)
unnamed: C19.1, U6.15 (Y)
unnamed: C20.1, U7.14 (X)
unnamed: C21.1, U7.15 (Y)

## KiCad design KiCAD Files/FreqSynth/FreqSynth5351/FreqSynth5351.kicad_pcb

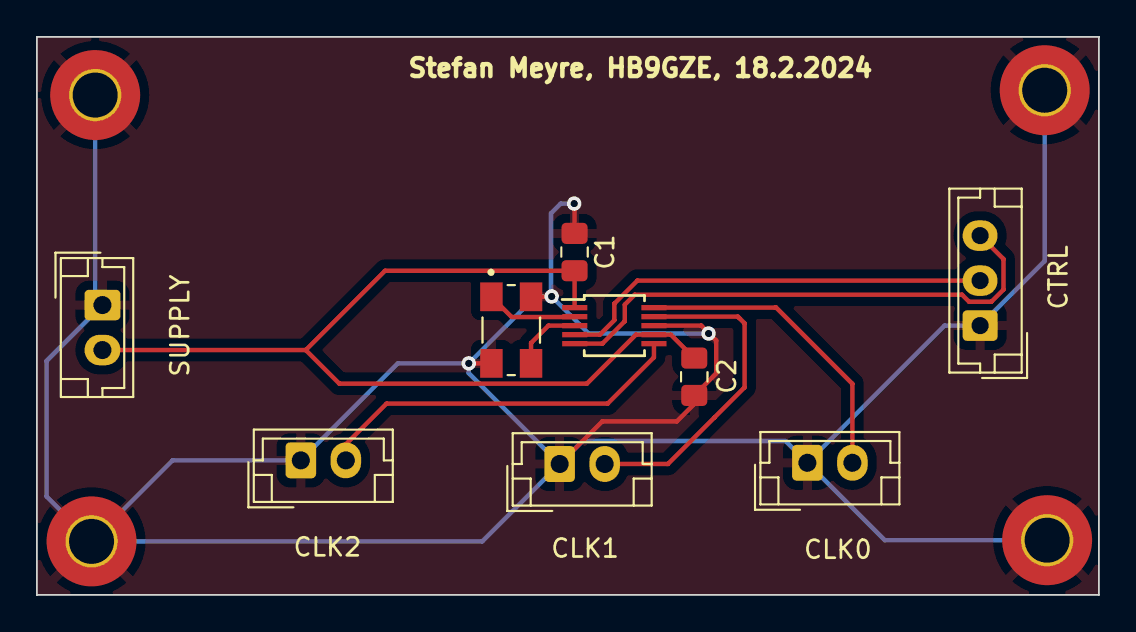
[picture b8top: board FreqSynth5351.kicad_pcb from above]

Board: 2 copper layers, 59.0 x 31.0 mm, 13 parts (0 on the bottom side), 9 nets.

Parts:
C1, C2: 100nF; C_0805_2012Metric_Pad1.18x1.45mm_HandSolder
CLK0, CLK1, CLK2: Conn_01x02_Socket; JST_EH_B2B-EH-A_1x02_P2.50mm_Vertical
CTRL: Conn_01x03_Socket; JST_EH_B3B-EH-A_1x03_P2.50mm_Vertical
H1, H2, H3, H4: MountingHole_Pad; MountingHole_2.5mm_Pad_TopBottom
SUPPLY: Conn_01x02_Socket; JST_EH_B2B-EH-A_1x02_P2.50mm_Vertical
U1: Si5351A-B-GT; MSOP-10_3x3mm_P0.5mm
Y1: ECS-250-8-30B-CKM; XTAL_ECS-250-8-30B-CKM

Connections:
+3.3V: C1.2, C2.2, SUPPLY.2, U1.1 (VDD), U1.7 (VDDO)
/SCL: CTRL.2, U1.4 (SCL)
/SDA: CTRL.3, U1.5 (SDA)
GND: C1.1, C2.1, CLK0.1, CLK1.1, CLK2.1, CTRL.1, H1.1, H2.1, H3.1, H4.1, SUPPLY.1, U1.8 (GND), Y1.2 (GND), Y1.4 (GND__1)
unnamed: CLK0.2, U1.10 (CLK0)
unnamed: CLK1.2, U1.9 (CLK1)
unnamed: CLK2.2, U1.6 (CLK2)
unnamed: U1.2 (XA), Y1.1 (IN/OUT)
unnamed: U1.3 (XB), Y1.3 (OUT/IN)

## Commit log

2024-12-09 UART works now
2024-12-09 stopped UART; increased dynGraph queue from 1 to 5
2024-12-10 Create README.md
    first edit
2024-12-10 edited readme.md
2024-12-10 deleted hpp file outside project
2024-12-12 20kHz sampling rate of FIR filter with 290 tabs
2024-12-17 minor changes; ready for Hilbert implementation
2024-12-17 minor things
